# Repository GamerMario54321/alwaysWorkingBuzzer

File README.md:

# alwaysWorkingBuzzer
Buzzer circuit that buzzes when the microcontroller sends a signal or if the microcontroller breaks/disconnects

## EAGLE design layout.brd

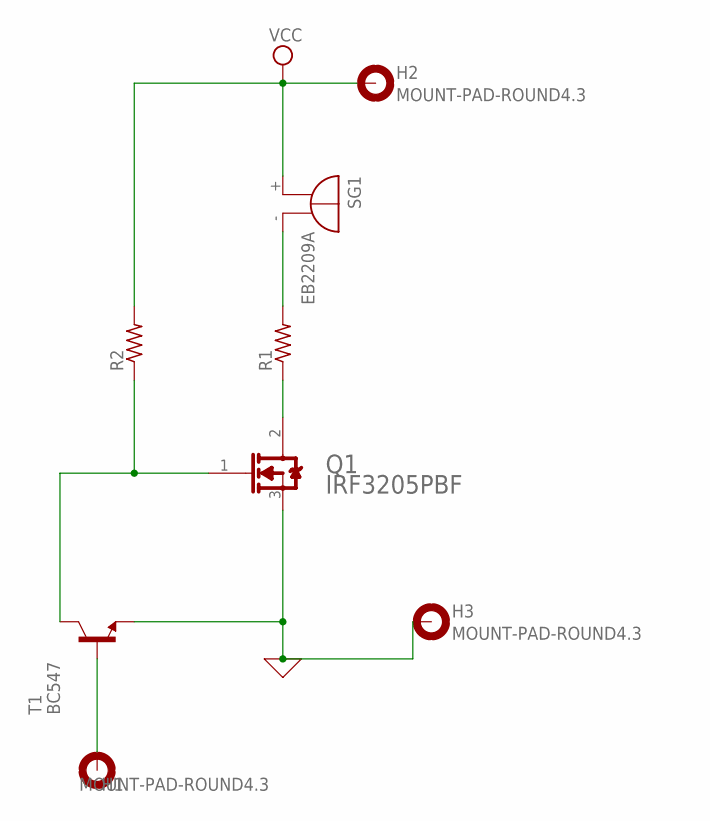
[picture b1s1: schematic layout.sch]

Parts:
H1, H2, H3: MOUNT-PAD-ROUND4.3; 4,3-PAD
Q1: INFINEON_IRF3205PBFINFINEON_IRF3205PBF_0_0; INFINEON_IRF3205PBF_0
R1, R2: R-US_RDH/15; RDH/15
SG1: EB2209A
T1: BC547; TO92

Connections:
0: H3.B4,3, Q1.3 (SOURCE), T1.1 (E)
unnamed: R1.2, SG1.-
unnamed: Q1.2 (DRAIN), R1.1
unnamed: Q1.1 (GATE), R2.1, T1.3 (C)
unnamed: H1.B4,3, T1.2 (B)
VCC: H2.B4,3, R2.2, SG1.+

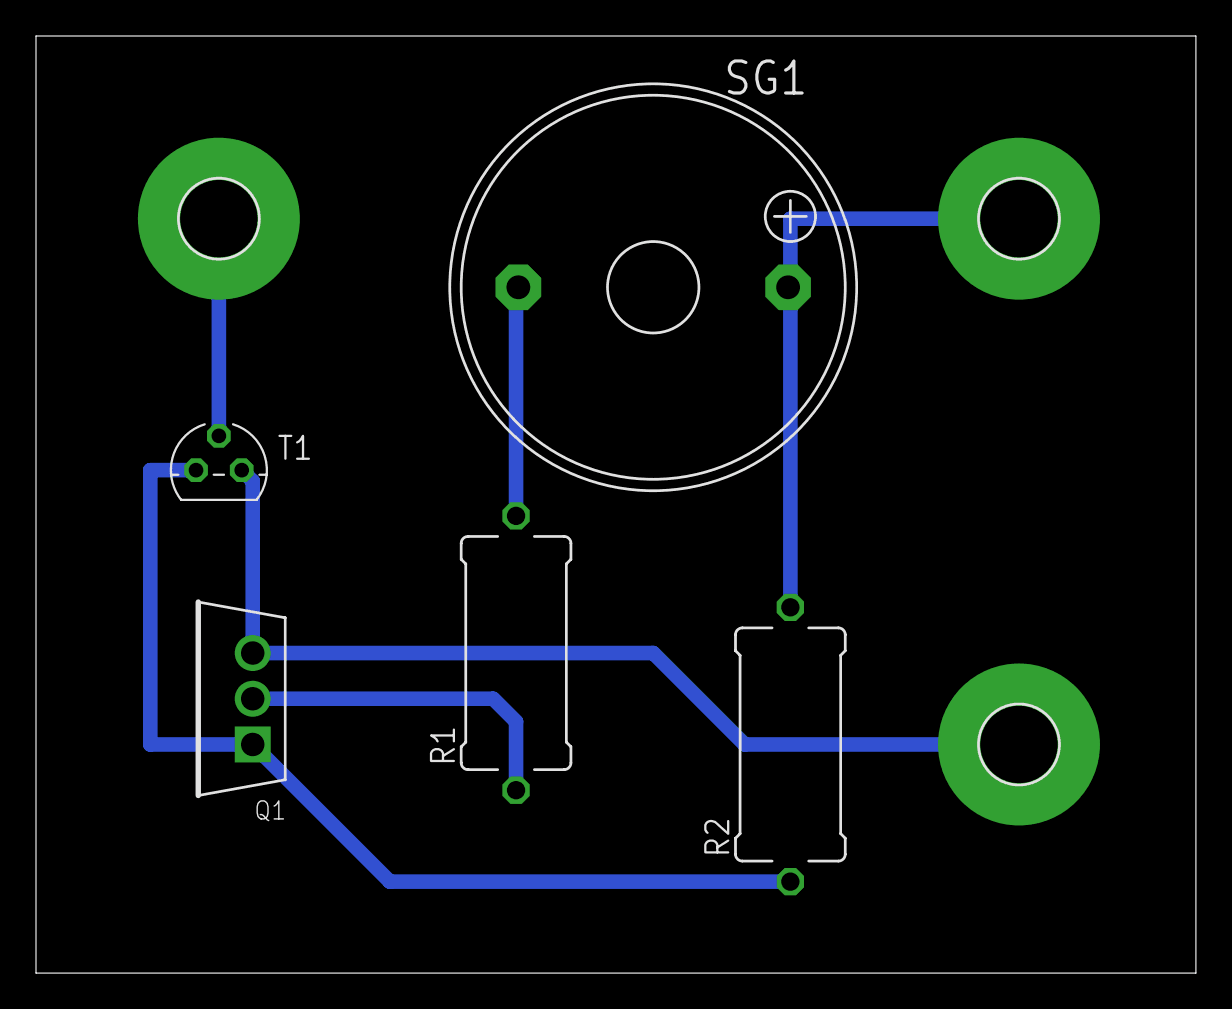
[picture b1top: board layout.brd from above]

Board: 2 copper layers, 64.4 x 52.1 mm, 8 parts (0 on the bottom side), 6 nets.
